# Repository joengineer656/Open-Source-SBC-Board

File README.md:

# Open-Source-SBC-Board

A custom single-board computer built around the Rockchip RK3576 SoC, designed as a learning project to explore modern SBC architecture.

> **Status: Work in Progress — v2 current.** Schematic in progress. Not yet fabricated. V2 schematics are not final – expect minor errors.

## Which version are you looking at?

**You are viewing `v2` (default, `main` branch).**

- **Want v1 (old)?** 
  - Switch branch: `archive/v1` in the GitHub branch dropdown, or
  - Download ZIP: [Releases → v1.0](https://github.com/joengineer656/Open-Source-SBC-Board/releases/tag/v1.0)
  - Clone specific: `git clone -b archive/v1 https://github.com/joengineer656/Open-Source-SBC-Board.git`
- **Want v2?** You're here. Or [Releases → v2.0](https://github.com/joengineer656/Open-Source-SBC-Board/releases/tag/v2.0) for ZIP.

| Version | Branch | Tag | Status |
|---------|--------|-----|--------|
| v2 (this page) | `main` | `v2.0` | active development, default view |
| v1 (archived) | `archive/v1` | `v1.0` | frozen, read-only |

## Overview

This board is a learning project exploring the design of a modern, feature-rich SBC. It combines a high-performance RK3576 application processor with an RP2350A companion MCU for IO offloading, targeting a balance between compute power and real-time IO capability.

V2 is a cleaned-up / upgraded version of the V1 design (ref: [devmeb0/RK3576-SBC](https://github.com/devmeb0/RK3576-SBC)). Main V2 deltas: **second Gigabit Ethernet port, M.2 Key-E socket for wireless modules (no FCC cert needed for the base board), onboard CR2032 RTC backup battery (not external), schematic cleanup + notes throughout.**

## Key Specifications (v2)

| Feature | Specification |
|---------|--------------|
| **SoC** | Rockchip RK3576 – 4x Cortex-A72 @ 2.2GHz + 4x Cortex-A53 @ 1.8GHz, Mali-G52 MC3, 6 TOPS NPU |
| **Companion MCU** | Raspberry Pi RP2350A (IO co-processor, USB-C, SWD/JTAG) |
| **RAM** | 32-bit LPDDR5 (Micron MT62F1G32D4DR-031) |
| **Storage** | UFS 2.0, eMMC 5.1 modular, µSD card, SPI flash (W25Q128 for MCU) |
| **Video Output** | HDMI 2.1 / eDP 1.3, USB-C DP1.4 Alt-Mode, 4-lane MIPI DSI + 0.96" OLED header |
| **Camera** | MIPI CSI 4-lane (or split 2+2) |
| **Networking** | Dual Gigabit Ethernet (2x RTL8211F, PoE optional), M.2 Key-E 67-pin for WiFi/BT |
| **USB** | 4x USB 3.2 Host (RTS5411 hub), 1x USB-C OTG/PD (FUSB302), 1x USB-C for MCU |
| **Expansion** | 40-pin RPi-compatible header, PCIe 2.1 x1 + SATA3 via FPC |
| **Display** | 0.96" OLED header (8-pin) |
| **RTC** | RV-3028-C7 + FRAM, onboard CR2032 holder (BAT-HLD-001) |
| **PMIC** | RK806S-5 + SY8388 / SY8089 DC/DCs |
| **Power In** | Barrel jack, USB-C 5V, USB-C PD, PoE option, 40-pin header |

## Features (v2)

**1. SoC – Rockchip RK3576 (FCCSP698)**
Octa-core big.LITTLE, Cortex-M0 for user code, Mali-G52 MC3 (OpenGL ES 3.2 / Vulkan 1.2 / OpenCL 2.1), 6 TOPS NPU (INT4/8/16, FP16/BF16/TF32), 16MP ISP with HDR/3DNR, 8K@30 / 4K@120 decode, 4K@60 encode. 2x RGMII, PCIe2.1/SATA3/USB3 combo lanes, 2x CAN-FD on-chip. OS: Linux / Android 14 / Yocto / Buildroot.

**2. Memory – 32-bit LPDDR5**
`LPDDR5.kicad_sch`: Micron MT62F1G32D4DR-031, 32-bit dual-channel layout per RK3576 reference.

**3. Storage – eMMC + UFS + microSD + SPI**
- `eMMC/UFS.kicad_sch` + `UFS/eMMC.kicad_sch`: eMMC 5.1 modular footprint + UFS 2.0 HS-G3.
- `uSD_Card.kicad_sch`: push-push microSD with AP2553 load-switch power + TPD4E ESD.
- `RP2350A.kicad_sch`: 2x W25Q128JVS SPI flash for the co-MCU.

**4. Display – 3x concurrent**
- `HDMI.kicad_sch`: HDMI 2.1 / eDP 1.3 combo, TPD4E05U06 ESD, TXB0104 translators, AP2553 5V switch.
- `USBC_SOC.kicad_sch`: USB-C Alt-Mode DP1.4 + USB3 combo, FUSB302 PD controller, TPS22953 switches.
- `MIPI.kicad_sch`: 4-lane MIPI DSI TX via 30-pin FPC, TXS0108 level-shifted.
- `oled_screen.kicad_sch`: 0.96" OLED 8-pin header for status/debug.

**5. Network – Dual GbE + M.2 Key-E (V2 highlight)**
- `Ethernet.kicad_sch`: 2x RTL8211F-CG PHYs (U25/U26, 2x 25 MHz crystals), LPJG0926HENL magjacks, PoE input headers (PoE optional).
- `Wireless.kicad_sch`: M.2 Key-E 67-pin socket APCI0108-P001A (LCSC C7498141), 0.5 mm right-angle, for off-the-shelf WiFi/BT modules – replaces soldered wireless, so the base board itself needs no FCC certification.

**6. USB**
- `USBA_Host.kicad_sch`: 4x USB3.2 Host via 2x RTS5411S-GR hubs, SY6280 current-limit per port, TPD4E ESD.
- `USBC_SOC.kicad_sch`: 1x USB-C OTG/Host Alt-Mode with PD negotiation – can also be power input.
- `RP2350A.kicad_sch`: separate USB-C 2.0 16P for the MCU.

**7. Camera**
`MIPI.kicad_sch`: MIPI CSI RX – 4-lane or split 2+2. Feeds RK3576 triple CSI + 16MP ISP.

**8. Power – RK806S-5 + discretes**
`Power.kicad_sch`: RK806S-5 PMIC, 2x SY8388ARHC + SY8089AAAC DC/DCs, AO3401 FETs, SMBJ TVS. Inputs: barrel-jack, USB-C 5V/3A-5A with UVLO/OVLO, USB-C PD in, PoE option, or 40-pin header 5V.

**9. RTC – onboard battery (V2 change)**
`RTC.kicad_sch`: RV-3028-C7 RTC + FM24C64/M24C64 FRAM/EEPROM, AO3401 OR-ing, fuse + SMBJ. CR2032 coin holder Linx BAT-HLD-001 **on-board** – V1 used an external JST battery.

**10. Expansion**
- `PCIe.kicad_sch` + `connectors.kicad_sch`: PCIe 2.1 x1 + SATA3 via TE 1-2199230-5 FPCs.
- `40pin_GPIO.kicad_sch`: Raspberry-Pi-compatible 40-pin header, 3x AP2553 load switches, SMBJ ESD: 28x GPIO / 13x PWM, 5x UART, 5x I2C, 1x I3C, 2x SPI, CAN, PDM, SDIO, 12-bit SAR-ADC 1MS/s, 3.3V out / 5V in-out.

**11. Co-MCU – RP2350A**
`RP2350A.kicad_sch`: RP2350A with ETA7014 regulators, W25Q128 flash, USB-C, SWD/JTAG header, tactile buttons. For real-time IO / housekeeping offload.

**12. Bring-up / mechanical**
`Fixtures.kicad_sch`: mounting holes, fiducials, test-point probes, UART/SWD debug header, boot DIP, maskrom + power tactiles, dual power/activity LEDs, active fan header.

## Architecture

```
┌─────────────────────────────────────────────────────┐
│                    RK3576 SoC                        │
│  ┌──────────┐  ┌──────────┐  ┌──────────────────┐  │
│  │  CPU     │  │  GPU     │  │  Memory Ctrl     │  │
│  │  (ARM)   │  │          │  │  (LPDDR5)        │  │
│  └──────────┘  ──────────┘  └──────────────────  │
│  ┌──────────  ┌──────────┐  ┌──────────────────┐  │
│  │  PCIe    │  │  USB 3.2 │  │  MIPI CSI/DSI    │  │
│  └──────────  └──────────┘  └──────────────────┘  │
│  ┌──────────┐  ┌──────────┐  ┌──────────────────┐  │
│  │  HDMI    │  │  Ethernet│  │  UFS/eMMC/SD     │  │
│  └──────────┘  └──────────┘  └──────────────────┘  │
└─────────────────────────────────────────────────────┘
         │                    │
         │ SPI/I2C/UART       │ USB
         ▼                    ▼
─────────────────┐   ┌─────────────────┐
│   RP2350A MCU   │   │   USB Hub       │
│  (IO offload)   │   │  (Host ports)   │
└─────────────────┘   └─────────────────┘
         │
         ▼
┌─────────────────┐
│  40-pin Header  │
│  (RPi compat)   │
└─────────────────┘
```

## Open in KiCad

Project file: `RK3576 SBCv2.kicad_pro` (KiCad 10.0)
Top sheet: `block_diagrame.kicad_sch` → `RK3576.kicad_sch` (SOC) + peripherals.

## Schematic Sheets (v2)

| Sheet | Description |
|-------|-------------|
| `block_diagrame.kicad_sch` | Top-level block diagram |
| `RK3576.kicad_sch` | RK3576 SoC, decoupling, strapping |
| `RP2350A.kicad_sch` | RP2350A companion MCU, USB-C, SWD |
| `Power.kicad_sch` | RK806S-5 PMIC and power distribution |
| `LPDDR5.kicad_sch` | LPDDR5 memory (Micron MT62F) |
| `Ethernet.kicad_sch` | Dual Gigabit Ethernet (2x RTL8211F, PoE) |
| `Wireless.kicad_sch` | M.2 Key-E 67-pin WiFi/BT socket |
| `HDMI.kicad_sch` | HDMI 2.1 output |
| `MIPI.kicad_sch` | MIPI DSI/CSI via FPC |
| `PCIe.kicad_sch` | PCIe 2.1 / SATA via FPC |
| `USBA_Host.kicad_sch` | 4x USB-A host (RTS5411 hub) |
| `USBC_SOC.kicad_sch` | USB-C to SoC, PD (FUSB302) |
| `uSD_Card.kicad_sch` | µSD card slot |
| `eMMC/UFS.kicad_sch` + `UFS/eMMC.kicad_sch` | eMMC / UFS storage |
| `RTC.kicad_sch` | RV-3028 RTC + onboard CR2032 |
| `oled_screen.kicad_sch` | 0.96" OLED header |
| `40pin_GPIO.kicad_sch` | RPi-compatible header |
| `connectors.kicad_sch`, `dc_power_soket.kicad_sch` | Power / debug connectors |
| `Fixtures.kicad_sch` | Test points, fiducials |
| `directive_labels.kicad_sch` | Netclass directives |

> Note: `eMMC/UFS.kicad_sch` and `UFS/eMMC.kicad_sch` names are swapped upstream — kept as-is to avoid breaking sheet references. Excluded from repo (per `.gitignore`): `.history/`, `Resources/`, `*.bak`, `*.lck`, `project.kicad_dru`, `.hs_rules.json`, lowercase dup placeholders (`fixtures`/`power`), empty orphans (`digital`, `mechanical`, `output`, `USBC_MCU`, `eMMC_UFS`).

## Repository Structure (v2 on `main`)

```
Open-Source-SBC-Board/ (main = v2)
├── RK3576 SBCv2.kicad_pro       # KiCad project file
├── RK3576 SBCv2.kicad_sch       # Project root sheet
├── RK3576 SBCv2.kicad_pcb       # PCB layout (in progress)
├── RK3576 SBCv2.kicad_prl
├── RK3576 SBCv2.kicad_dru
├── *.kicad_sch                  # Hierarchical schematic sheets
├── eMMC/ UFS/                   # Storage sheets
├── LICENSE                      # CERN-OHL-P v2
├── README.md                     # This file
└── .gitignore                    # KiCad ignores (*.bak, .lck, .history/)
```

v1 lives only on branch `archive/v1` + tag `v1.0`, not in this tree.

## Design Goals

1. **Learn modern SBC design** — power delivery, high-speed interfaces (LPDDR5, UFS, PCIe, USB 3.2), mixed-signal layout
2. **Real-time IO capability** — RP2350A handles time-critical tasks independently of the Linux-running SoC
3. **Rich connectivity** — Dual Ethernet, M.2 Key-E WiFi/BT, USB, PCIe, MIPI, HDMI in a compact form factor
4. **Open source** — full schematic and PCB released under CERN-OHL-P

## For maintainers: how versions are stored

```bash
# v1 frozen
git branch archive/v1   # from old main
git tag v1.0 archive/v1

# v2 is main
git tag v2.0 main

# push all (needs auth)
git push origin archive/v1 v1.0 main v2.0
gh release create v1.0 --target archive/v1 --title "v1.0 - archived" --notes "Frozen v1. See branch archive/v1."
gh release create v2.0 --target main --title "v2.0 - current" --notes "Current v2. Default branch main."
```

Users get v2 by default, v1 via branch dropdown or Releases ZIP — i.e. “2 repos in 1 repo”.

## License

This hardware design is licensed under the **CERN Open Hardware Licence Version 2 — Permissive** (CERN-OHL-P v2).

See [LICENSE](LICENSE) for the full text.

## Acknowledgments

- [Rockchip](https://www.rock-chips.com/) for the RK3576 SoC
- [Raspberry Pi](https://www.raspberrypi.com/) for the RP2350A
- [KiCad](https://www.kicad.org/) for the EDA tools
- [CERN](https://ohwr.org/project/cernohl/) for the OHL license
- [devmeb0/RK3576-SBC](https://github.com/devmeb0/RK3576-SBC) V1 reference design

---

*This is a learning project. The design has not been fabricated or tested yet. Use at your own risk.*

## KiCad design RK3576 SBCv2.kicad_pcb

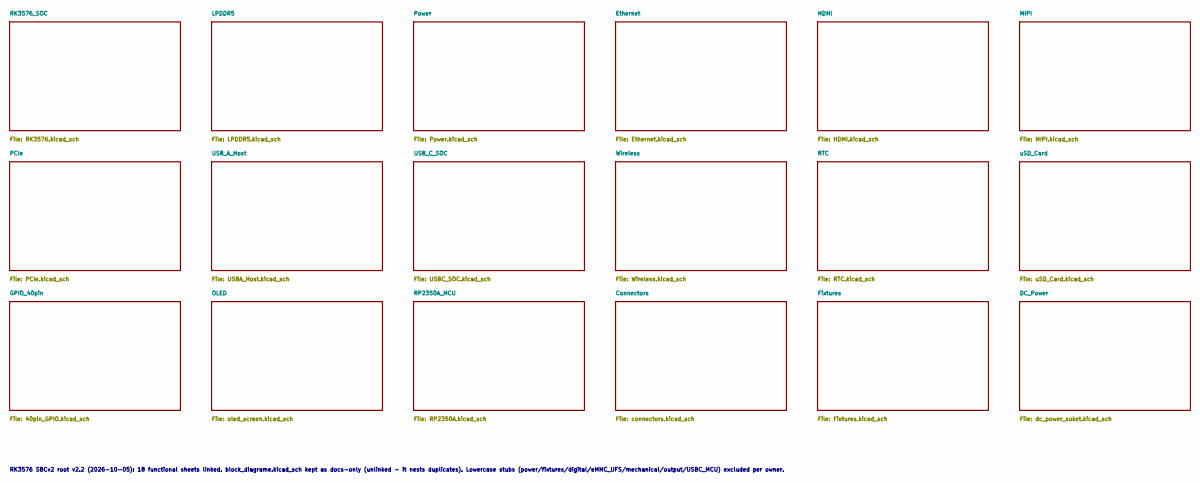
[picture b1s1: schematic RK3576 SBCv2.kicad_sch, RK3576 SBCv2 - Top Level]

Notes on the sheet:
RK3576 SBCv2 root v2.2 (2026-10-05): 18 functional sheets linked. block_diagrame.kicad_sch kept as docs-only (unlinked - it nests duplicates). Lowercase stubs (power/fixtures/digital/eMMC_UFS/mechanical/output/USBC_MCU) excluded per owner.

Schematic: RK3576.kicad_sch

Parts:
C1, C10: 12pF; C_0402_1005Metric; Mouser Part 187-CL05C120JB5NNNC; LCSC Part C26406
C2, C3, C4, C5, C6, C48, C49, C50, C106, C107, C108, C109, C110, C111: 22u; C_0603_1608Metric; Mouser Part CL10A226MP8NUNE; LCSC Part C86295
C7, C8, C9, C11, C13, C14, C15, C16, C18, C19, C20, C21, C22, C23, C28, C35, C36, C37, C38, C39, C40, C42, C47, C51, C53, C54, C55, C56, C57, C59, C60, C61, C62, C63, C64, C65, C66, C67, C68, C69, C70, C71, C72, C73, C74, C75, C76, C77, C78, C79, C80, C81, C82, C83, C84, C85, C86, C87, C88, C89, C90, C91, C92, C93, C94, C95, C96, C97, C98, C99, C100, C101, C102, C103, C104: 1u; C_0201_0603Metric_Pad0.64x0.40mm_HandSolder; Mouser Part CL03A105KP3NSNC; LCSC Part C5209398
C12, C17, C41, C43, C44, C45, C46, C52, C58: 10u; C_0603_1608Metric; Mouser Part 187-CL10A106KP8NNNC; LCSC Part C19702
C24, C25, C26, C27, C29, C30, C31, C32, C33, C34: 100n; C_0201_0603Metric_Pad0.64x0.40mm_HandSolder; Mouser Part 187-CL03A104KO3NNND; LCSC Part C307380
C105, C112: 18pF; C_0402_1005Metric; Mouser Part 603-CC402FRNPO9BN180; LCSC Part C541431
D1, D2: PESD5V0S1BA; D_SOD-323_TVS; Mouser Part 771-PESD5V0S1BA-T/R; LCSC Part C5158048
D3: SMBJ5.0CA; D_SMB_TVS; Mouser Part 581-SMBJ5.0CA; LCSC Part C113975
J1: B4B Connector; FanPinHeader_1x04_P2.54mm_Vertical; Mouser Part 306-B4BXHALFSN; LCSC Part C144395
LED1, LED2: XL-1608SURC-06; LED_0603_1608Metric; LCSC Part C965799
Q1: 2SK3018; SOT-323_SC-70; LCSC Part C20069148
R1: 4.7k; R_0402_1005Metric; Mouser Part 603-RC0402FR-074K7L; LCSC Part C105871; not fitted
R2, R30, R31, R32, R34: 22R; R_0402_1005Metric; Mouser Part 603-RC0402FR-070RL; LCSC Part C106231
R3, R5, R6, R26, R28: 4.7k; R_0402_1005Metric; Mouser Part 603-RC0402FR-074K7L; LCSC Part C105871
R4, R33: 510k; R_0402_1005Metric; Mouser Part 603-RC0402FR-07510KL; LCSC Part C137961
R7, R233: 0R; R_0402_1005Metric; Mouser Part 603-RC0402FR-070RL; LCSC Part C106231
R8, R9: 100R; R_0402_1005Metric; Mouser Part 603-RC0402FR-0722RL; LCSC Part C114765
R10, R18, R19, R20, R21, R22, R23: 10k; R_0402_1005Metric; Mouser Part 603-RC0402FR-0710KL; LCSC Part C60490
R11, R13, R14: 1k; R_0402_1005Metric; Mouser Part 603-RC0402FR-071KL; LCSC Part C106235
R12: 100k; R_0402_1005Metric; Mouser Part 603-RC0402FR-0710KL; LCSC Part C60490
R15: 6.8k; R_0402_1005Metric; Mouser Part 603-RC0402FR-076K8L; LCSC Part C93940
R16: 23.2k; R_0402_1005Metric; Mouser Part 603-AC0402FR-0723K2L; LCSC Part C226362
R17: 88.7k; R_0402_1005Metric; Mouser Part 603-RC0402FR-0788K7L; LCSC Part C477808
R24, R25, R35: 8.2k; R_0402_1005Metric; Mouser Part 603-RT0402FRE078K2L; LCSC Part C136971
R27, R29: 200R; R_0402_1005Metric; Mouser Part 603-RT0402FRE07200RL; LCSC Part C854192
SW1: DSHP03TS-S; SW_DIP_SPSTx03_Slide_KingTek_DSHP03TJ_W5.25mm_P1.27mm_JPin; LCSC Part C319051
SW2: XUNPU TS-1089S-02526; LCSC Part C455282
U1: RK3576; FCCSP-698_L17.2-W16.1-TL_RK3576; MPN RK3576; LCSC Part C42388007
Y1: TXM24M0004322FBCDO00T; Crystal_SMD_3225-4Pin_3.2x2.5mm; LCSC Part C362340
Y2: XTM32026000FT00351001; Crystal_SMD_3225-4Pin_3.2x2.5mm; LCSC Part C37635380

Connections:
/40pin GPIO/I2C8_SCL_M3_RTC_EEPROM: U1.A11 (I2C8_SCL_M3); also elsewhere on the board
/40pin GPIO/I2C8_SDA_M3_RTC_EEPROM: U1.A13 (I2C8_SDA_M3); also elsewhere on the board
/40pin GPIO/SPI1_{MCU}.CS: R6.2, U1.1E7 (GPIO3_D7_d); also elsewhere on the board
/40pin GPIO/SPI1_{MCU}.SCK: R1.2, U1.1E12 (SPI3_CLK_M1); also elsewhere on the board
/40pin GPIO/SPI1_{MCU}.SDI: R5.2, U1.1C10 (SPI3_MOSI_M1); also elsewhere on the board
/40pin GPIO/SPI1_{MCU}.SDO: R3.2, U1.1D10 (SPI3_MISO_M1); also elsewhere on the board
/Ethernet/ETH0_{PHY}.MDC: U1.1B13 (ETH1_MDC_M0); also elsewhere on the board
/Ethernet/ETH0_{PHY}.MDIO: U1.1B15 (ETH1_MDIO_M0); also elsewhere on the board
/Ethernet/ETH0_{PHY}.RXC: U1.1C18 (ETH0_RXCLK_M1); also elsewhere on the board
/Ethernet/ETH0_{PHY}.RXCTL: U1.1A20 (ETH0_RXCTL_M1); also elsewhere on the board
/Ethernet/ETH0_{PHY}.RXD0: U1.B22 (ETH0_RXD0_M1); also elsewhere on the board
/Ethernet/ETH0_{PHY}.RXD1: U1.1A19 (ETH0_RXD1_M1); also elsewhere on the board
/Ethernet/ETH0_{PHY}.RXD2: U1.B21 (ETH0_RXD2_M1); also elsewhere on the board
/Ethernet/ETH0_{PHY}.RXD3: U1.A21 (ETH0_RXD3_M1); also elsewhere on the board
/Ethernet/ETH0_{PHY}.TXC: U1.1B16 (ETH0_TXCLK_M1); also elsewhere on the board
/Ethernet/ETH0_{PHY}.TXCTL: U1.B20 (ETH0_TXCTL_M1); also elsewhere on the board
/Ethernet/ETH0_{PHY}.TXD0: U1.1A18 (ETH0_TXD0_M1); also elsewhere on the board
/Ethernet/ETH0_{PHY}.TXD1: U1.B19 (ETH0_TXD1_M1); also elsewhere on the board
/Ethernet/ETH0_{PHY}.TXD2: U1.A19 (ETH0_TXD2_M1); also elsewhere on the board
/Ethernet/ETH0_{PHY}.TXD3: U1.1A17 (ETH0_TXD3_M1); also elsewhere on the board
/Ethernet/ETH0_{PHY}_CLK_{OUT}: U1.1E15 (ETH_CLK0_25M_OUT_M1); also elsewhere on the board
/Ethernet/ETH0_{PHY}_INT: U1.1C6 (GPIO4_A3_d); also elsewhere on the board
/Ethernet/ETH0_{PHY}_nRST: U1.1D6 (GPIO4_A2_d); also elsewhere on the board
/Ethernet/ETH1_{PHY}.MDC: U1.1B18 (ETH0_MDC_M1); also elsewhere on the board
/Ethernet/ETH1_{PHY}.MDIO: U1.1D16 (ETH0_MDIO_M1); also elsewhere on the board
/Ethernet/ETH1_{PHY}.RXC: U1.1D15 (ETH1_RXCLK_M0); also elsewhere on the board
/Ethernet/ETH1_{PHY}.RXCTL: U1.B18 (ETH1_RXCTL_M0); also elsewhere on the board
/Ethernet/ETH1_{PHY}.RXD0: U1.1A16 (ETH1_RXD0_M0); also elsewhere on the board
/Ethernet/ETH1_{PHY}.RXD1: U1.B17 (ETH1_RXD1_M0); also elsewhere on the board
/Ethernet/ETH1_{PHY}.RXD2: U1.A17 (ETH1_RXD2_M0); also elsewhere on the board
/Ethernet/ETH1_{PHY}.RXD3: U1.1A15 (ETH1_RXD3_M0); also elsewhere on the board
/Ethernet/ETH1_{PHY}.TXC: U1.1C15 (ETH1_TXCLK_M0); also elsewhere on the board
/Ethernet/ETH1_{PHY}.TXCTL: U1.B16 (ETH1_TXCTL_M0); also elsewhere on the board
/Ethernet/ETH1_{PHY}.TXD0: U1.1A14 (ETH1_TXD0_M0); also elsewhere on the board
/Ethernet/ETH1_{PHY}.TXD1: U1.B15 (ETH1_TXD1_M0); also elsewhere on the board
/Ethernet/ETH1_{PHY}.TXD2: U1.A15 (ETH1_TXD2_M0); also elsewhere on the board
/Ethernet/ETH1_{PHY}.TXD3: U1.1A13 (ETH1_TXD3_M0); also elsewhere on the board
/Ethernet/ETH1_{PHY}_CLK_{OUT}: U1.1D18 (ETH_CLK1_25M_OUT_M0); also elsewhere on the board
/Ethernet/ETH1_{PHY}_INT: U1.1B6 (GPIO4_A5_d); also elsewhere on the board
/Ethernet/ETH1_{PHY}_nRST: U1.1C5 (GPIO4_A4_d); also elsewhere on the board
/HDMI/HDMI_PWREN_H: U1.AK1 (GPIO4_C5_d); also elsewhere on the board
/HDMI/HDMI_TX_CEC_M0: U1.AK3 (HDMI_TX_CEC_M0); also elsewhere on the board
/HDMI/HDMI_TX_HPDIN_M0: U1.AK2 (HDMI_TX_HPDIN_M0); also elsewhere on the board
/HDMI/HDMI_TX_ON: U1.AL3 (GPIO4_C4_d); also elsewhere on the board
/HDMI/HDMI_TX_SCL: U1.AL2 (HDMI_TX_SCL); also elsewhere on the board
/HDMI/HDMI_TX_SDA: U1.1AE2 (HDMI_TX_SDA); also elsewhere on the board
/LPDDR5/LPDDR5_A.CA0: U1.T1 (LP5_A0_A); also elsewhere on the board
/LPDDR5/LPDDR5_A.CA1: U1.1N1 (LP5_A1_A); also elsewhere on the board
/LPDDR5/LPDDR5_A.CA2: U1.1R3 (LP5_A2_A); also elsewhere on the board
/LPDDR5/LPDDR5_A.CA3: U1.1T2 (LP5_A3_A); also elsewhere on the board
/LPDDR5/LPDDR5_A.CA4: U1.1M5 (LP5_A4_A); also elsewhere on the board
/LPDDR5/LPDDR5_A.CA5: U1.1P5 (LP5_A5_A); also elsewhere on the board
/LPDDR5/LPDDR5_A.CA6: U1.1R5 (LP5_A6_A); also elsewhere on the board
/LPDDR5/LPDDR5_A.CK_N: U1.P1 (LP5_CLKN_A); also elsewhere on the board
/LPDDR5/LPDDR5_A.CK_P: U1.1L1 (LP5_CLKP_A); also elsewhere on the board
/LPDDR5/LPDDR5_A.CS0: U1.1N3 (LP5_CSN0_A); also elsewhere on the board
/LPDDR5/LPDDR5_A.CS1: U1.1N5 (LP5_CSN1_A); also elsewhere on the board
/LPDDR5/LPDDR5_A.DMI0: U1.1V1 (LP5_DMI0_A); also elsewhere on the board
/LPDDR5/LPDDR5_A.DMI1: U1.AE1 (LP5_DMI1_A); also elsewhere on the board
/LPDDR5/LPDDR5_A.DQ0: U1.W1 (LP5_DQ0_A); also elsewhere on the board
/LPDDR5/LPDDR5_A.DQ1: U1.1T1 (LP5_DQ1_A); also elsewhere on the board
/LPDDR5/LPDDR5_A.DQ2: U1.1P1 (LP5_DQ2_A); also elsewhere on the board
/LPDDR5/LPDDR5_A.DQ3: U1.U1 (LP5_DQ3_A); also elsewhere on the board
/LPDDR5/LPDDR5_A.DQ4: U1.1V3 (LP5_DQ4_A); also elsewhere on the board
/LPDDR5/LPDDR5_A.DQ5: U1.1W4 (LP5_DQ5_A); also elsewhere on the board
/LPDDR5/LPDDR5_A.DQ6: U1.AC1 (LP5_DQ6_A); also elsewhere on the board
/LPDDR5/LPDDR5_A.DQ7: U1.AB1 (LP5_DQ7_A); also elsewhere on the board
/LPDDR5/LPDDR5_A.DQ8: U1.AF1 (LP5_DQ8_A); also elsewhere on the board
/LPDDR5/LPDDR5_A.DQ9: U1.1AB1 (LP5_DQ9_A); also elsewhere on the board
/LPDDR5/LPDDR5_A.DQ10: U1.1AD1 (LP5_DQ10_A); also elsewhere on the board
/LPDDR5/LPDDR5_A.DQ11: U1.AH1 (LP5_DQ11_A); also elsewhere on the board
/LPDDR5/LPDDR5_A.DQ12: U1.1Y1 (LP5_DQ12_A); also elsewhere on the board
/LPDDR5/LPDDR5_A.DQ13: U1.1W2 (LP5_DQ13_A); also elsewhere on the board
/LPDDR5/LPDDR5_A.DQ14: U1.1AA3 (LP5_DQ14_A); also elsewhere on the board
/LPDDR5/LPDDR5_A.DQ15: U1.1AA1 (LP5_DQ15_A); also elsewhere on the board
/LPDDR5/LPDDR5_A.RDQS0_N: U1.Y1 (LP5_RDQS0N_A); also elsewhere on the board
/LPDDR5/LPDDR5_A.RDQS0_P: U1.1U1 (LP5_RDQS0P_A); also elsewhere on the board
/LPDDR5/LPDDR5_A.RDQS1_N: U1.1AB3 (LP5_RDQS1N_A); also elsewhere on the board
/LPDDR5/LPDDR5_A.RDQS1_P: U1.1AB4 (LP5_RDQS1P_A); also elsewhere on the board
/LPDDR5/LPDDR5_A.WCK0_N: U1.1V4 (LP5_WCK0N_A); also elsewhere on the board
/LPDDR5/LPDDR5_A.WCK0_P: U1.1V5 (LP5_WCK0P_A); also elsewhere on the board
/LPDDR5/LPDDR5_A.WCK1_N: U1.1AA5 (LP5_WCK1N_A); also elsewhere on the board
/LPDDR5/LPDDR5_A.WCK1_P: U1.1AA6 (LP5_WCK1P_A); also elsewhere on the board
/LPDDR5/LPDDR5_B.CA0: U1.L1 (LP5_A0_B); also elsewhere on the board
/LPDDR5/LPDDR5_B.CA1: U1.1J1 (LP5_A1_B); also elsewhere on the board
/LPDDR5/LPDDR5_B.CA2: U1.1J3 (LP5_A2_B); also elsewhere on the board
/LPDDR5/LPDDR5_B.CA3: U1.1G2 (LP5_A3_B); also elsewhere on the board
/LPDDR5/LPDDR5_B.CA4: U1.1F4 (LP5_A4_B); also elsewhere on the board
/LPDDR5/LPDDR5_B.CA5: U1.1K5 (LP5_A5_B); also elsewhere on the board
/LPDDR5/LPDDR5_B.CA6: U1.1H5 (LP5_A6_B); also elsewhere on the board
/LPDDR5/LPDDR5_B.CK_N: U1.N1 (LP5_CLKN_B); also elsewhere on the board
/LPDDR5/LPDDR5_B.CK_P: U1.1K1 (LP5_CLKP_B); also elsewhere on the board
/LPDDR5/LPDDR5_B.CS0: U1.1K2 (LP5_CSN0_B); also elsewhere on the board
/LPDDR5/LPDDR5_B.CS1: U1.1M3 (LP5_CSN1_B); also elsewhere on the board
/LPDDR5/LPDDR5_B.DMI0: U1.B4 (LP5_DMI0_B); also elsewhere on the board
/LPDDR5/LPDDR5_B.DMI1: U1.1B1 (LP4_DMI1_B); also elsewhere on the board
/LPDDR5/LPDDR5_B.DQ0: U1.1D2 (LP5_DQ0_B); also elsewhere on the board
/LPDDR5/LPDDR5_B.DQ1: U1.1F2 (LP5_DQ1_B); also elsewhere on the board
/LPDDR5/LPDDR5_B.DQ2: U1.1G1 (LP5_DQ2_B); also elsewhere on the board
/LPDDR5/LPDDR5_B.DQ3: U1.K1 (LP5_DQ3_B); also elsewhere on the board
/LPDDR5/LPDDR5_B.DQ4: U1.1C3 (LP5_DQ4_B); also elsewhere on the board
/LPDDR5/LPDDR5_B.DQ5: U1.1B3 (LP5_DQ5_B); also elsewhere on the board
/LPDDR5/LPDDR5_B.DQ6: U1.A5 (LP5_DQ6_B); also elsewhere on the board
/LPDDR5/LPDDR5_B.DQ7: U1.G1 (LP5_DQ7_B); also elsewhere on the board
/LPDDR5/LPDDR5_B.DQ8: U1.1A1 (LP5_DQ8_B); also elsewhere on the board
/LPDDR5/LPDDR5_B.DQ9: U1.B1 (LP5_DQ9_B); also elsewhere on the board
/LPDDR5/LPDDR5_B.DQ10: U1.B2 (LP5_DQ10_B); also elsewhere on the board
/LPDDR5/LPDDR5_B.DQ11: U1.A2 (LP5_DQ11_B); also elsewhere on the board
/LPDDR5/LPDDR5_B.DQ12: U1.1E1 (LP5_DQ12_B); also elsewhere on the board
/LPDDR5/LPDDR5_B.DQ13: U1.1C1 (LP5_DQ13_B); also elsewhere on the board
/LPDDR5/LPDDR5_B.DQ14: U1.E1 (LP5_DQ14_B); also elsewhere on the board
/LPDDR5/LPDDR5_B.DQ15: U1.D1 (LP5_DQ15_B); also elsewhere on the board
/LPDDR5/LPDDR5_B.RDQS0_N: U1.1F1 (LP5_RDQS0N_B); also elsewhere on the board
/LPDDR5/LPDDR5_B.RDQS0_P: U1.H1 (LP5_RDQS0P_B); also elsewhere on the board
/LPDDR5/LPDDR5_B.RDQS1_N: U1.B3 (LP5_RDQS1N_B); also elsewhere on the board
/LPDDR5/LPDDR5_B.RDQS1_P: U1.A3 (LP5_RDQS1P_B); also elsewhere on the board
/LPDDR5/LPDDR5_B.WCK0_N: U1.1G4 (LP5_WCK0N_B); also elsewhere on the board
/LPDDR5/LPDDR5_B.WCK0_P: U1.1G5 (LP5_WCK0P_B); also elsewhere on the board
/LPDDR5/LPDDR5_B.WCK1_N: U1.1E4 (LP5_WCK1N_B); also elsewhere on the board
/LPDDR5/LPDDR5_B.WCK1_P: U1.1D4 (LP5_WCK1P_B); also elsewhere on the board
/LPDDR5/LPDDR5_nRTS: U1.1U5 (LP5_RESET); also elsewhere on the board
/MIPI/CAM1_CLK1_OUT_M0_1V8: U1.1C12 (GPIO3_D0_d); also elsewhere on the board
/MIPI/CAM1_CLK2_OUT_M0_1V8: U1.1A12 (GPIO3_D1_d); also elsewhere on the board
/MIPI/DSI0.TX_D2_P: U1.AL18 (MIPI_DPHY_DSI_TX_D2P); also elsewhere on the board
/MIPI/LCD_BL_PWM1_CH1_M0: U1.AD29 (PWM1_CH1_M0); also elsewhere on the board
/MIPI/LCD_PWREN_H: U1.1W23 (GPIO0_D0_d); also elsewhere on the board
/MIPI/MIPI_DPHY_CS2_CAM1_PDN_H: U1.1A10 (GPIO3_D2_d); also elsewhere on the board
/MIPI/MIPI_DPHY_CSI_CAM1_PDN_H: U1.1B7 (CAM_CLK2_OUT_M0); also elsewhere on the board
/MIPI/MIPI_DPHY_CSI_CAM2_RST_H: U1.1B12 (CAM_CLK1_OUT_M0); also elsewhere on the board
/PCIe/PCIE0.REFCLK_N: U1.1N23 (PCIE0_REFCLKN); also elsewhere on the board
/PCIe/PCIE0.REFCLK_P: U1.1N22 (PCIE0_REFCLKP); also elsewhere on the board
/PCIe/PCIE0.RX_N: U1.R29 (PCIE0_RXN); also elsewhere on the board
/PCIe/PCIE0.RX_P: U1.R28 (PCIE0_RXP); also elsewhere on the board
/PCIe/PCIE0.TX_N: U1.P28 (PCIE0_TXN); also elsewhere on the board
/PCIe/PCIE0.TX_P: U1.P29 (PCIE0_TXP); also elsewhere on the board
/PCIe/PCIE0_CLKREQ_L: U1.1A6 (SAI1_SDI0_M0); also elsewhere on the board
/PCIe/PCIE0_DET_L: U1.1A4 (SPDIF_TX0_M0); also elsewhere on the board
/PCIe/PCIE0_WAKE_L: U1.B8 (SPDIF_RX0_M0); also elsewhere on the board
/PCIe/PCIE0_nRST: U1.B6 (SAI1_SDO3_M0); also elsewhere on the board
/Power/I2C1_SCL_M0_RK806: U1.1T22 (I2C1_SCL_M0); also elsewhere on the board
/Power/I2C1_SDA_M0_RK806: U1.1T23 (I2C1_SDA_M0); also elsewhere on the board
/Power/PMIC_INT_L: U1.1T21 (PMIC_INT), U1.V29 (GPIO0_A0_d); also elsewhere on the board
/Power/PMIC_PWRON_L: U1.Y29 (GPIO0_A5_d); also elsewhere on the board
/Power/PMIC_PWR_CTRL1: U1.Y28 (PWR_CTRL1); also elsewhere on the board
/Power/PMIC_PWR_CTRL2: U1.1T24 (PWR_CTRL2); also elsewhere on the board
/Power/PMIC_nRST: R233.2; also elsewhere on the board
/RK3576 SOC/40GPIOs_GPIO(3_A6)_UART(1)_RX-M2: U1.1A7 (UART1_RX_M2)
/RK3576 SOC/40GPIOs_GPIO(3_A7)_UART(1)_TX-M2: U1.B13 (UART1_TX_M2)
/RK3576 SOC/40GPIOs_GPIO(3_B0)_UART(10)_RX-M0: U1.B14 (UART10_RX_M0)
/RK3576 SOC/40GPIOs_GPIO(3_B1)_UART(10)_TX-M0: U1.1A11 (UART10_TX_M0)
/RK3576 SOC/40GPIOs_GPIO(3_B4)_PWM(1)_CH4-M3: U1.B10 (PWM1_CH4_M3)
/RK3576 SOC/40GPIOs_GPIO(3_B5)_PWM(1)_CH5-M3: U1.1A9 (PWM1_CH5_M3)
/RK3576 SOC/40GPIOs_GPIO(3_B6)_PWM(0)_CH1-M3: U1.B11 (PWM0_CH1_M3)
/RK3576 SOC/40GPIOs_GPIO(3_B7)_UART(2)_RX-M2: U1.1D12 (UART2_RX_M2)
/RK3576 SOC/40GPIOs_GPIO(3_C0)_UART(2)_TX-M2: U1.1E9 (UART2_TX_M2)
/RK3576 SOC/40GPIOs_GPIO(3_C1)_I2C(5)_SDA-M3: U1.1B10 (I2C5_SDA_M3)
/RK3576 SOC/40GPIOs_GPIO(3_C2)_I2C(9)_SCL-M3: U1.B9 (I2C9_SCL_M3)
/RK3576 SOC/40GPIOs_GPIO(3_C3)_I2C(9)_SDA-M3: U1.1A8 (I2C9_SDA_M3)
/RK3576 SOC/40GPIOs_GPIO(3_C4)_I2C(5)_SCL-M3: U1.1D9 (I2C5_SCL_M3)
/RK3576 SOC/40GPIOs_GPIO(3_C5)_PWM(2)_CH2-M3: U1.1B9 (PWM2_CH2_M3)
/RK3576 SOC/40GPIOs_GPIO(3_C6): U1.1D7 (GPIO3_C6_d)
/RK3576 SOC/40GPIOs_GPIO(3_C7): U1.1C7 (GPIO3_C7_d)
/RK3576 SOC/BT_REG_ON_L: U1.1W21 (GPIO0_C3_d); also elsewhere on the board
/RK3576 SOC/BT_WAKE_DEV_L: U1.1C22 (GPIO1_C7_d); also elsewhere on the board
/RK3576 SOC/BT_WAKE_HOST_L: U1.1E21 (GPIO1_D4_d); also elsewhere on the board
/RK3576 SOC/CSI1_RX_CLK_N: U1.1AD22 (MIPI_DPHY_CSI2_RX_CLKN)
/RK3576 SOC/CSI1_RX_CLK_P: U1.1AD21 (MIPI_DPHY_CSI2_RX_CLKP)
/RK3576 SOC/CSI1_RX_D0_N: U1.AE28 (MIPI_DPHY_CSI1_RX_D0N)
/RK3576 SOC/CSI1_RX_D0_P: U1.AE29 (MIPI_DPHY_CSI1_RX_D0P)
/RK3576 SOC/CSI1_RX_D1_N: U1.AF28 (MIPI_DPHY_CSI1_RX_D1N)
/RK3576 SOC/CSI1_RX_D1_P: U1.AF29 (MIPI_DPHY_CSI1_RX_D1P)
/RK3576 SOC/CSI1_RX_D2_N: U1.AG28 (MIPI_DPHY_CSI1_RX_D2N)
/RK3576 SOC/CSI1_RX_D2_P: U1.AG29 (MIPI_DPHY_CSI1_RX_D2P)
/RK3576 SOC/CSI1_RX_D3_N: U1.AH28 (MIPI_DPHY_CSI1_RX_D3N)
/RK3576 SOC/CSI1_RX_D3_P: U1.AH29 (MIPI_DPHY_CSI1_RX_D3P)
/RK3576 SOC/CSI2_RX_CLK_N: U1.1AC23 (MIPI_DPHY_CSI1_RX_CLKN)
/RK3576 SOC/CSI2_RX_CLK_P: U1.1AC22 (MIPI_DPHY_CSI1_RX_CLKP)
/RK3576 SOC/EEPROM_WP: U1.1D13 (GPIO3_A4_d); also elsewhere on the board
/RK3576 SOC/FSPI0_CLE/EMMC_DATA_STROBE: U1.1F23 (EMMC_STRB); also elsewhere on the board
/RK3576 SOC/FSPI0_DS/EMMC_CLK_OUT: U1.1G23 (EMMC_CLK); also elsewhere on the board
/RK3576 SOC/FSPI0_WPn/EMMC_nRST: U1.1D23 (EMMC_RSTN); also elsewhere on the board
/RK3576 SOC/FSPI0/EMMC.CMD: U1.1F22 (EMMC_CMD)
/RK3576 SOC/FSPI0/EMMC.D0: U1.E28 (EMMC_D0)
/RK3576 SOC/FSPI0/EMMC.D1: U1.E29 (EMMC_D1)
/RK3576 SOC/FSPI0/EMMC.D2: U1.1C24 (EMMC_D2)
/RK3576 SOC/FSPI0/EMMC.D3: U1.F28 (EMMC_D3)
/RK3576 SOC/FSPI0/EMMC.D4: U1.1D24 (EMMC_D4)
/RK3576 SOC/FSPI0/EMMC.D5: U1.G28 (EMMC_D5)
/RK3576 SOC/FSPI0/EMMC.D6: U1.D28 (EMMC_D6)
/RK3576 SOC/FSPI0/EMMC.D7: U1.1B24 (EMMC_D7)
/RK3576 SOC/HDMI.CK_N: U1.AK26 (HDMI_TX_D3N)
/RK3576 SOC/HDMI.CK_P: U1.AL26 (HDMI_TX_D3P)
/RK3576 SOC/HDMI.D0_N: U1.AK27 (HDMI_TX_D0N)
/RK3576 SOC/HDMI.D0_P: U1.1AE24 (HDMI_TX_D0P)
/RK3576 SOC/HDMI.D1_N: U1.AL28 (HDMI_TX_D1N)
/RK3576 SOC/HDMI.D1_P: U1.AK28 (HDMI_TX_D1P)
/RK3576 SOC/HDMI.D2_N: U1.AK29 (HDMI_TX_D2N)
/RK3576 SOC/HDMI.D2_P: U1.AJ28 (HDMI_TX_D2P)
/RK3576 SOC/HDMI.TX_SBD_N: U1.2U12 (HDMI_TX_SBDN)
/RK3576 SOC/HDMI.TX_SBD_P: U1.2T12 (HDMI_TX_SBDP)
/RK3576 SOC/HDMI_REXT: R24.1, U1.1AA20 (HDMI_TX_REXT)
/RK3576 SOC/I2C2_SCL_M0_USB_Wireless: U1.1W24 (I2C2_SCL_M0); also elsewhere on the board
/RK3576 SOC/I2C2_SDA_M0_USB_Wireless: U1.AB29 (I2C2_SDA_M0); also elsewhere on the board
/RK3576 SOC/JTAG_TCK_M1 & UART0_TX_M0: J1.2, R8.2
/RK3576 SOC/JTAG_TMS_M1 & UART0_RX_M0: D1.2 (A), D2.2 (A), J1.3, R9.2
/RK3576 SOC/RESET_L: C38.1, R7.1, R10.2, R233.1, U1.W28 (NPOR)
/RK3576 SOC/RTC_32KOUT_SOC: U1.1U23 (CLK_32K_IN); also elsewhere on the board
/RK3576 SOC/RTC_INT_L: U1.A9 (GPIO3_A5_d); also elsewhere on the board
/RK3576 SOC/SAI2.LRCK_M0: U1.1A24 (SAI2_LRCK_M0)
/RK3576 SOC/SAI2.SCLK_M0: U1.1D22 (SAI2_SCLK_M0)
/RK3576 SOC/SAI2.SDI_M0: U1.C28 (SAI2_SDI_M0)
/RK3576 SOC/SAI2.SDO_M0: U1.C29 (SAI2_SDO_M0)
/RK3576 SOC/SARADC_VIN0_BOOT: C64.1, R18.2, SW1.4, SW1.5, SW1.6, U1.A25 (SARADC_IN0_BOOT)
/RK3576 SOC/SARADC_VIN1_KEY/RECOVERY: C65.1, D3.2 (A), R19.2, SW2.2, U1.1A22 (SARADC_IN1)
/RK3576 SOC/SARADC_VIN2_HW_ID: C66.1, R22.2, R23.1, U1.1B19 (SARADC_IN2)
/RK3576 SOC/SARADC_VIN3_HP_HOOK: C67.1, U1.1C19 (SARADC_IN3)
/RK3576 SOC/SARADC_VIN4_IN: C68.1, U1.1E18 (SARADC_IN4); also elsewhere on the board
/RK3576 SOC/SARADC_VIN5_BOM_ID: C69.1, R20.2, R21.1, U1.1D19 (SARADC_IN5)
/RK3576 SOC/SARADC_VIN6: C70.1, U1.1D21 (SARADC_IN6)
/RK3576 SOC/SARADC_VIN7_DC: C71.1, U1.1E19 (SARADC_IN7)
/RK3576 SOC/SDMMC1.CLK_M0: U1.1B22 (SDMMC1_CLK_M0); also elsewhere on the board
/RK3576 SOC/SDMMC1.CMD_M0: U1.B26 (SDMMC1_CMD_M0); also elsewhere on the board
/RK3576 SOC/SDMMC1.D0_M0: U1.A28 (SDMMC1_D0_M0)
/RK3576 SOC/SDMMC1.D1_M0: U1.B27 (SDMMC1_D1_M0)
/RK3576 SOC/SDMMC1.D2_M0: U1.1A23 (SDMMC1_D2_M0)
/RK3576 SOC/SDMMC1.D3_M0: U1.A27 (SDMMC1_D3_M0)
/RK3576 SOC/TSADC_CTRL_M0: R7.2, U1.1R24 (TSADC_CTRL_M0)
/RK3576 SOC/UART4.CTSN_M1: U1.B29 (UART4_RTSN_M1)
/RK3576 SOC/UART4.RTSN_M1: U1.1C23 (UART4_CTSN_M1)
/RK3576 SOC/UART4.RX_M1: U1.1B23 (UART4_TX_M1)
/RK3576 SOC/UART4.TX_M1: U1.B28 (UART4_RX_M1)
/RK3576 SOC/UFS3.1_TX_REXT: R35.1, U1.2R2 (UFS_TX_REXT)
/RK3576 SOC/UFS.RX0_N: U1.AL7 (UFS_RX_D0N); also elsewhere on the board
/RK3576 SOC/UFS.RX0_P: U1.AK8 (UFS_RX_D0P); also elsewhere on the board
/RK3576 SOC/UFS.RX1_N: U1.AL6 (UFS_RX_D1N); also elsewhere on the board
/RK3576 SOC/UFS.RX1_P: U1.AK7 (UFS_RX_D1P); also elsewhere on the board
/RK3576 SOC/UFS.TX0_N: U1.1AC6 (UFS_TX_D0N); also elsewhere on the board
/RK3576 SOC/UFS.TX0_P: U1.1AD6 (UFS_TX_D0P); also elsewhere on the board
/RK3576 SOC/UFS.TX1_N: U1.1AD5 (UFS_TX_D1N); also elsewhere on the board
/RK3576 SOC/UFS.TX1_P: U1.1AD4 (UFS_TX_D1P); also elsewhere on the board
/RK3576 SOC/UFS_REF_{CLK}: U1.AK4 (UFS_REFCLK); also elsewhere on the board
/RK3576 SOC/UFS_nRST: U1.1AD2 (UFS_RSTN); also elsewhere on the board
/RK3576 SOC/USB_{HOST}_PWREN_H: U1.1A5 (SAI1_SDO1_M0); also elsewhere on the board
/RK3576 SOC/USB_{HUB}.D_N: U1.2T5 (USB2_OTG1_DM); also elsewhere on the board
/RK3576 SOC/USB_{HUB}.D_P: U1.2T4 (USB2_OTG1_DP); also elsewhere on the board
/RK3576 SOC/USB_{HUB}.SSRX1_N: U1.M29 (USB3_OTG1_SSRXN)
/RK3576 SOC/USB_{HUB}.SSRX1_P: U1.M28 (USB3_OTG1_SSRXP)
/RK3576 SOC/USB_{HUB}.SSTX1_N: U1.N29 (USB3_OTG1_SSTXN)
/RK3576 SOC/USB_{HUB}.SSTX1_P: U1.N28 (USB3_OTG1_SSTXP)
/RK3576 SOC/USB_{SOC}.AUX_N: U1.2T3 (DP_TX_AUXN)
/RK3576 SOC/USB_{SOC}.AUX_P: U1.2T2 (DP_TX_AUXP)
/RK3576 SOC/USB_{SOC}.D_N: U1.AL9 (USB2_OTG0_DM); also elsewhere on the board
/RK3576 SOC/USB_{SOC}.D_P: U1.AK9 (USB2_OTG0_DP); also elsewhere on the board
/RK3576 SOC/USB_{SOC}.PUPDCTRL1: U1.1B5 (GPIO4_A6_d); also elsewhere on the board
/RK3576 SOC/USB_{SOC}.PUPDCTRL2: U1.A7 (GPIO4_A7_d); also elsewhere on the board
/RK3576 SOC/USB_{SOC}.RX1_N: U1.AL10 (USB3_OTG0_SSRX1N)
/RK3576 SOC/USB_{SOC}.RX1_P: U1.AK10 (USB3_OTG0_SSRX1P)
/RK3576 SOC/USB_{SOC}.RX2_N: U1.AL12 (USB3_OTG0_SSRX2N)
/RK3576 SOC/USB_{SOC}.RX2_P: U1.AK12 (USB3_OTG0_SSRX2P)
/RK3576 SOC/USB_{SOC}.TX1_N: U1.AK11 (USB3_OTG0_SSTX1N)
/RK3576 SOC/USB_{SOC}.TX1_P: U1.AL11 (USB3_OTG0_SSTX1P)
/RK3576 SOC/USB_{SOC}.TX2_N: U1.AK13 (USB3_OTG0_SSTX2N)
/RK3576 SOC/USB_{SOC}.TX2_P: U1.AL13 (USB3_OTG0_SSTX2P)
/RK3576 SOC/USB_{SOC}_CON_INT: U1.B7 (SAI1_SDO2_M0); also elsewhere on the board
/RK3576 SOC/USB_{SOC}_PWREN_H: U1.AJ1 (GPIO4_C7_d); also elsewhere on the board
/RK3576 SOC/USB_{SOC}_REXT: R25.1, U1.2T7 (USB3_OTG0_REXT)
/RK3576 SOC/USER_LED: R11.1, U1.1AA23 (GPIO0_D3_d)
/RK3576 SOC/Vdet_USB_{MCU}: U1.B12 (GPIO3_D3_d); also elsewhere on the board
/RK3576 SOC/Vdet_USB_{SOC}: U1.1AE1 (GPIO4_C6_d); also elsewhere on the board
/RK3576 SOC/WIFI_REG_ON_L: U1.1W22 (GPIO0_C4_d); also elsewhere on the board
/RK3576 SOC/WIFI_WAKE_DEV_L: U1.1E22 (GPIO1_D5_d); also elsewhere on the board
/RK3576 SOC/WIFI_WAKE_HOST_L: U1.A26 (GPIO1_C6_d); also elsewhere on the board
/RK3576 SOC/WIFI_nRST: U1.1AA22 (GPIO0_C5_d); also elsewhere on the board
/RK3576 SOC/WIRELESS_ALERT_L: U1.1Y21 (GPIO0_C6_d); also elsewhere on the board
/RK3576 SOC/uSD.CLK: U1.1B21 (SDMMC0_CLK)
/RK3576 SOC/uSD.CMD: U1.1A21 (SDMMC0_CMD)
/RK3576 SOC/uSD.D0: U1.B24 (SDMMC0_D0)
/RK3576 SOC/uSD.D1: U1.B25 (SDMMC0_D1)
/RK3576 SOC/uSD.D2: U1.A23 (SDMMC0_D2)
/RK3576 SOC/uSD.D3: U1.B23 (SDMMC0_D3)
/RK3576 SOC/uSD_DET: U1.1U21 (SDMMC0_DETN); also elsewhere on the board
/RK3576 SOC/uSD_PWREN_H: U1.1Y24 (SDMMC0_PWREN); also elsewhere on the board
unnamed: C1.1, R2.1, Y1.1
unnamed: C112.1, R34.2, Y2.1
unnamed: LED1.2 (A), R13.2
unnamed: LED1.1 (K), Q1.3 (D)
unnamed: LED2.2 (A), R14.2
unnamed: Q1.1 (G), R11.2, R12.1
unnamed: R15.2, SW1.1
unnamed: R16.2, SW1.2
unnamed: R17.2, SW1.3
unnamed: R32.1, U1.2C2 (DDRPHY_PLL_AVSS)
unnamed: R31.1, U1.1R6 (ZQ_A)
unnamed: R30.1, U1.1J6 (ZQ_B)
unnamed: C10.1, R4.2, U1.U28 (OSC_XIN), Y1.3
unnamed: R2.2, R4.1, U1.U29 (OSC_XOUT)
unnamed: R9.1, U1.AA28 (UART0_RX_M0)
unnamed: R8.1, U1.1U24 (UART0_TX_M0)
unnamed: C86.1, U1.2N7 (MIPI_DCPHY_VREG)
unnamed: R33.1, R34.1, U1.AK5 (OSC_UFS_XIN)
unnamed: C105.1, R33.2, U1.AL5 (OSC_UFS_XOUT), Y2.3
unnamed: R27.1, U1.2R3 (USB2_OTG0_REXT)
unnamed: R26.1, U1.2P3 (USB2_OTG0_VBUSDET)
unnamed: R29.1, U1.2U8 (USB2_OTG1_REXT)
unnamed: R28.1, U1.2T10 (USB2_OTG1_VBUSDET)
VCCA_1.8v_S0: C13.1, C14.1, C15.1, U1.2H12 (PLL_AVDD1V8), U1.2J10 (OSC_AVDD1V8), U1.2K11 (PMUIO0_VCC1V8)
VCCA_1V8_S3: C16.1, C21.1, U1.2A7 (VCCIO4_VCC), U1.2B10 (VCCIO3_VCC); also elsewhere on the board
VCC_1.8v_S3: R10.1
VCC_3.3v_S0: C8.1, C28.1, C47.1, C62.1, C63.1, C72.1, J1.1, U1.1U20 (PMUIO1_VCC), U1.2A2 (VCCIO2_VCC), U1.2A4 (VCCIO5_VCC[2]), U1.2A5 (VCCIO5_VCC[2]), U1.2A8 (VCCIO1_VCC), U1.2N3 (VCCIO6_VCC); also elsewhere on the board
VDD2_DDR_S3: C104.1, U1.2B2 (DDRPHY_CKE_VDDQ); also elsewhere on the board
VDDA0V75_HDMI_S0: C52.1, C55.1, U1.2N11 (HDMI_TX_EDP_TX_AVDDD0V75), U1.2P11 (HDMI_TX_EDP_TX_AVDDC0V75); also elsewhere on the board
VDDA_0.75v_S0: C7.1, U1.2G11 (PLL_DVDD0V75)
VDDA_0V75_S0: C53.1, C54.1, C73.1, C74.1, C75.1, C76.1, C79.1, C80.1, U1.2D11 (MIPI_DPHY_CSI3/4_RX_AVDD0V75), U1.2H11 (OTP_DVDD0V75), U1.2L11 (MIPI_DPHY_CSI1/2_RX_AVDD0V75), U1.2M7 (MIPI_DCPHY_AVDD), U1.2P5 (USB2_OTG_DVDD0V75); also elsewhere on the board
VDDA_0V85_S0: C56.1, C85.1, C87.1, C89.1, C90.1, U1.2E11 (PCIE1_SATA1_USB3_OTG1_AVDD0V85), U1.2F11 (PCIE0_SATA0_AVDD0V85), U1.2M5 (USB3_OTG0_DP_TX_AVDD0V85), U1.2N2 (UFS_AVDD0V85), U1.2N5 (USB3_OTG0_DP_TX_DVDD0V85); also elsewhere on the board
VDDA_1V2_S0: C78.1, C88.1, U1.2M3 (VCCIO7_VCC), U1.2M8 (MIPI_DCPHY_AVDD1V2); also elsewhere on the board
VDDA_DDR_PLL_S0: C103.1, U1.2C3 (DDRPHY_PLL_DVDD); also elsewhere on the board
VDD_3.3v_S3: C9.1, C11.1, U1.2L2 (PMU_LOGIC_DVDD0V75[2]), U1.2L10 (PMU_LOGIC_DVDD0V75[2])
VDD_CPU_BIG_S0: C29.1, C32.1, C35.1, C39.1, C42.1, C45.1, C48.1, U1.2G5 (CPU_BIG_DVDD[8]), U1.2G6 (CPU_BIG_DVDD[8]), U1.2H6 (CPU_BIG_DVDD[8]), U1.2H7 (CPU_BIG_DVDD[8]), U1.2J6 (CPU_BIG_DVDD[8]), U1.2J7 (CPU_BIG_DVDD[8]), U1.2K6 (CPU_BIG_DVDD[8]), U1.2K7 (CPU_BIG_DVDD[8]); also elsewhere on the board
VDD_CPU_LIT_S0: C2.1, C5.1, C17.1, C19.1, C22.1, C25.1, U1.2H4 (CPU_LIT_DVDD[5]), U1.2J3 (CPU_LIT_DVDD[5]), U1.2J4 (CPU_LIT_DVDD[5]), U1.2K3 (CPU_LIT_DVDD[5]), U1.2K4 (CPU_LIT_DVDD[5]); also elsewhere on the board
VDD_DDR_S0: C97.1, C99.1, C101.1, C107.1, C109.1, C111.1, U1.2E2 (DDRPHY_DVDD[5]), U1.2F3 (DDRPHY_DVDD[5]), U1.2G2 (DDRPHY_DVDD[5]), U1.2G3 (DDRPHY_DVDD[5]), U1.2H2 (DDRPHY_DVDD[5]); also elsewhere on the board
VDD_GPU_S0: C31.1, C34.1, C37.1, C41.1, C44.1, C50.1, U1.2C4 (GPU_DVDD[5]), U1.2C5 (GPU_DVDD[5]), U1.2D4 (GPU_DVDD[5]), U1.2D5 (GPU_DVDD[5]), U1.2E4 (GPU_DVDD[5]); also elsewhere on the board
VDD_LOGIC_S0: C3.1, C23.1, C26.1, C30.1, C33.1, C36.1, C40.1, C43.1, C46.1, C49.1, U1.2E7 (LOGIC_DVDD[7]), U1.2F7 (LOGIC_MEM_DVDD[2]), U1.2F8 (LOGIC_DVDD[7]), U1.2F9 (LOGIC_DVDD[7]), U1.2G8 (LOGIC_DVDD[7]), U1.2G9 (LOGIC_DVDD[7]), U1.2H8 (LOGIC_DVDD[7]), U1.2H9 (LOGIC_DVDD[7]), U1.2J9 (LOGIC_MEM_DVDD[2]); also elsewhere on the board
VDD_NPU_S0: C4.1, C6.1, C12.1, C18.1, C20.1, C24.1, C27.1, U1.2C7 (NPU_DVDD[5]), U1.2C8 (NPU_DVDD[5]), U1.2C9 (NPU_DVDD[5]), U1.2D7 (NPU_DVDD[5]), U1.2D8 (NPU_DVDD[5]); also elsewhere on the board

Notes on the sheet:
ELECTROSTATIC-SENSITIVE DEVICE
HOT SURFACE
Notes
High Performance System
RK3576 MIPI (CSI/DCI)
Warnings
Power Source
SDIO 3.0 VDD_{IO5}
Internal DCDC Controls
VDD_{LDO}
VDD_{IO5}
VDD_{IO6}
Internal Systems
GPIOs 0-3
MIPI Physical
RK3576 USB2 (OTG/HUB)
Internal LDOs
RK3576 SARADC
1.65V ~ 3.6V
GPIOs 16-23
Fig. 2
VDD_{PSRAM0} VDD_{PSRAM1}
SARADC_VIN2_HW_ID: identifies the board revision SARADC_VIN5_BOM_ID: identifies the BOM That is not a security features it is a normal information
RK3576 (USB3 OTG/DP)
3.0V ~ 3.6V
2.97V ~ 3.63V
Internal Physical Layer
GPIOs 4-15
GPIOs 49-54
CSI0 for one High performance camera CSI1/2 for 2 cameras lower performance
Documentation Block
Fig. 1
VDD_{MIPI}
2.5V ~ 3.6V
VDD_{MIPI_DPHY}
GPIOs Group
RK3576 GPIO3 (40GPIO)
RK3576 HDMI
VDD_{IO0}
0.99V ~ 1.3V

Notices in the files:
parts and their libraries:
License: Apache-2.0
